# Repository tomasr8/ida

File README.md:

# Ida - 3-key macropad

# Table of Contents

- [Bill of Materials](#bill-of-materials)
- [Getting the parts made](#getting-the-parts-made)
- [Build guide](#build-guide)
- [Programming](#programming)
- [Schematics](#schematics)

# Bill of Materials

- **2x** 12x1 pin header
- **1x** Diode (_1N4148 DO-35_)
- **1x** Push button for resetting the board (_4x4x1.5mm_)
- **1x** Pro Micro or something with compatible pinout
- **3x** Keyboard switch
- **1x** 2u stabilizer
- **4x** 8mm rubber feet
- **3x** M2.5 screws
- Steady hands

# Getting the parts made

## PCB 

The gerbers are included in the repo in the [kicad](kicad/) directory. You can simply upload the gerbers to a service like JLCPCB.

Not that the entire Kicad project is included so you can also regenerate the gerbers with different settings if needed or adjust the PCB.

## Case

The case was CNC'd out of aluminium (again by JLCPCB). The case is made up of two ([top](top.stl), [bottom](bottom.stl)) parts.

The two parts are held together using 3 M2.5 screws. There is also a [drawing](drawing.pdf) showing the exact placement of the threads.

It might be possible to 3D print the case, but the screw threads might make it difficult.

# Build guide

**Step 1**: Solder the reset switch and the diode:

**Step 2**: Solder the pin headers:

**Step 3**: Place the stabilizers:

**Step 4**: Place switches in the enclosure:

**Step 5**: Place the PCB inside the enclosure and solder the switches:

**Step 6**: Place and solder the Pro Micro:

**Step 7**: Screw the bottom part of the case:

**Done!**

# Programming

I use QMK for programming the macropad. You can use my fork of QMK to change the keymap:
https://github.com/tomasr8/qmk_firmware/tree/ida/keyboards/ida

# Schematics

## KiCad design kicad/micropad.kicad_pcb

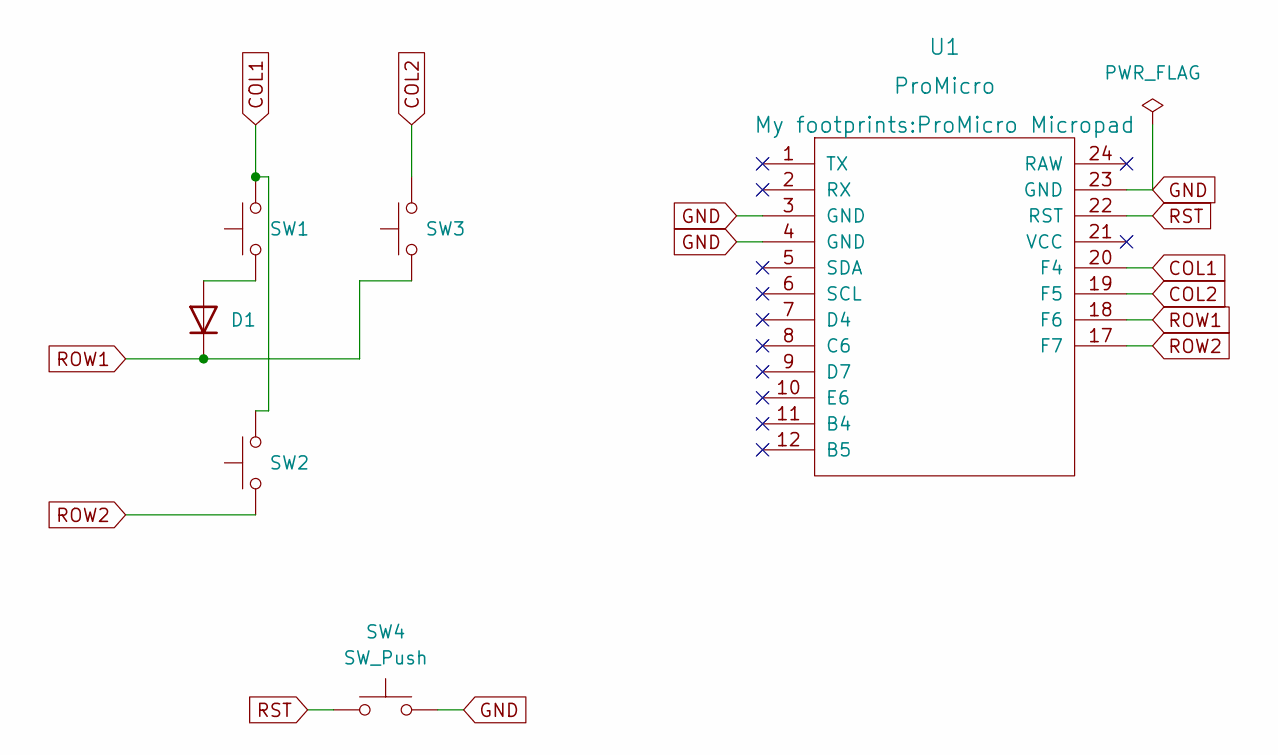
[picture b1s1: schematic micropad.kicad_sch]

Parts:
D1: 1N4148; D_DO-35_SOD27_P7.62mm_Horizontal
SW1, SW2: SW_Push; SW_Cherry_MX_Plate
SW3: SW_Push; SW_Cherry_MX_Plate_2.00u
SW4: SW_Push; SW_SPST_SKQG_WithoutStem
U1: ProMicro; ProMicro Micropad

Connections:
COL1: SW1.2, SW2.2, U1.20 (F4)
COL2: SW3.2, U1.19 (F5)
GND: SW4.2, U1.3 (GND), U1.4 (GND), U1.23 (GND)
unnamed: D1.2 (A), SW1.1
ROW1: D1.1 (K), SW3.1, U1.18 (F6)
ROW2: SW2.1, U1.17 (F7)
RST: SW4.1, U1.22 (RST)

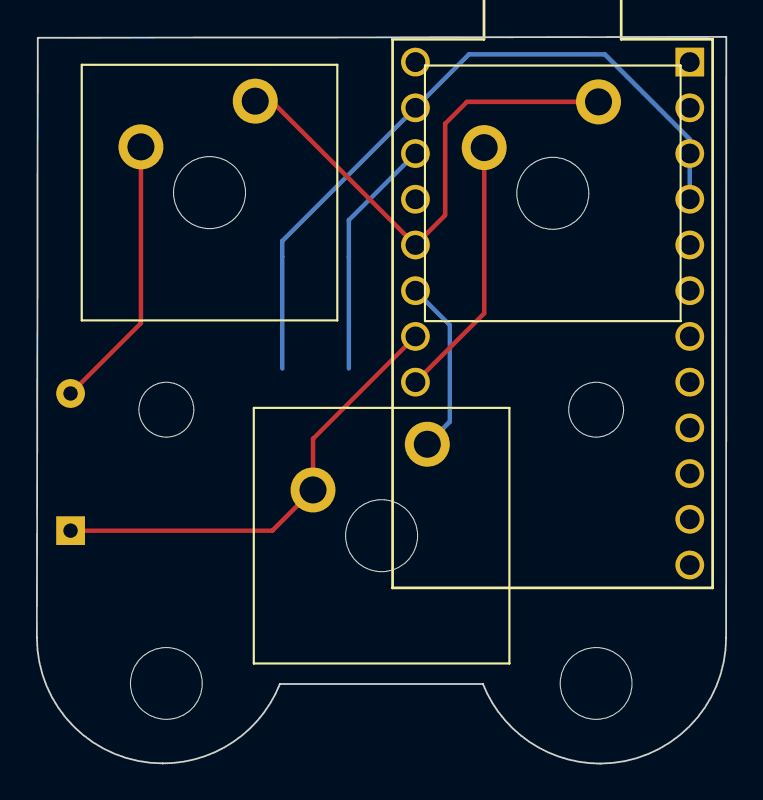
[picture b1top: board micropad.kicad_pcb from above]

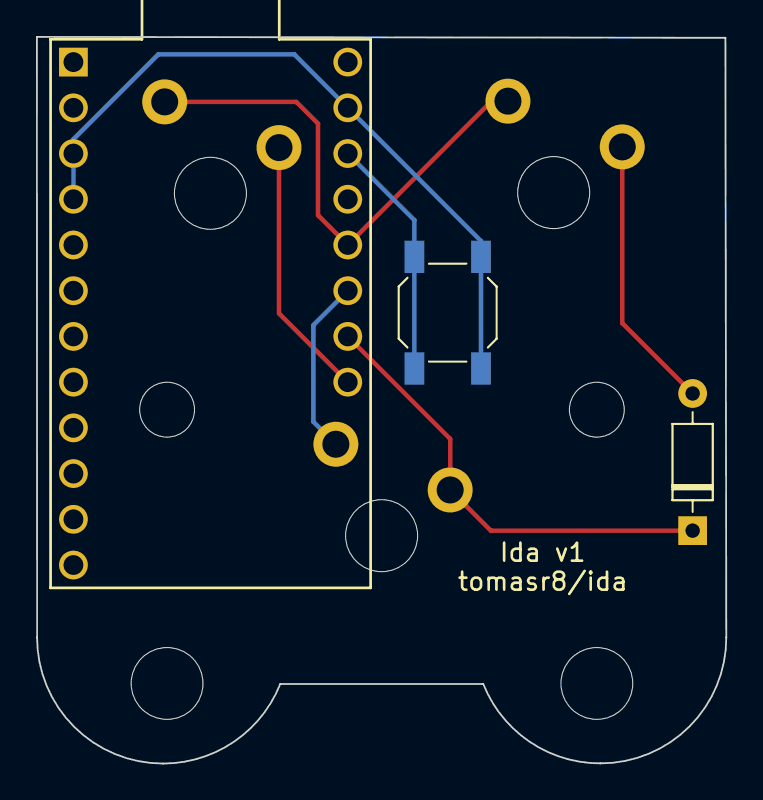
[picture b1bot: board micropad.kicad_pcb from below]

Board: 2 copper layers, 38.3 x 40.4 mm, 6 parts (3 on the bottom side), 7 nets.

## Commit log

2024-10-26 Add files
2025-05-31 images
